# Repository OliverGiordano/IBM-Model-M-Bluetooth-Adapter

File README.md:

# IBM Model M Bluetooth Adapter

A Bluetooth adapter for the IBM Model M PS/2 keyboard. The adapter converts PS/2 signals from the keyboard to HID signals that are sent over Bluetooth to a computer.

<div align="center">

</div>

---

## Project Goals

When I started this project I wanted to create a wireless way for my IBM Model M keyboard to connect to my Apple computer. When I use the adapter I bought off Amazon, my MacBook thought my keyboard was a barcode reader, which was not ideal.

---

## Project Iterations

### Iteration 1 — Custom Controller Replacement

My first attempt was to replace the control board on my keyboard entirely with a custom solution. The main advantage of this method was power efficiency — the giant microcontroller in the Model M is very old and eats energy. When plugged into a desktop this doesn't cause a problem, but on a limited battery it could be an issue.

<div align="center">

</div>

After some initial testing I chose to scrap this idea for a few reasons:

- I needed to disassemble the keyboard every time I wanted to work on the adapter, then reassemble it every time I wanted to use it.
- The membrane requires 26 GPIO ports to interface with the matrix. This was doable with an I2C GPIO extender, but it made the breadboarded prototype very difficult to debug since each connection was a new point of failure.
- It required using terrible membrane connectors.

<div align="center">

</div>

---

### Iteration 2 — PS/2 Adapter

My second iteration was creating an adapter that plugs into the Model M's PS/2 output. This was very convenient because I could cut one head off an existing adapter and directly break out the wiring. This solution is easy to wire and test because the PS/2 standard only has 4 wires: Data, Clock, 5V, and GND.

<div align="center">

</div>

For this project I chose to use the **Adafruit Feather ESP32**. I chose this microcontroller because it has built-in Bluetooth and a built-in battery circuit, and it was only around $8 — great for my budget.

One problem I didn't realize when picking it was that the Model M and the PS/2 standard require 5V input, but the Feather only supplies 3.3V. Because of this, I currently pull power for the PS/2 directly from the 5V USB line, which means the adapter needs to be plugged into a power source for now since the battery cannot supply 5V. In the future I plan to add a voltage booster for the 3.3V line, but it hasn't arrived yet.

Since reading 5V on the Feather would destroy the microcontroller, I use **voltage dividers** on the Data and Clock lines. Each divider consists of 3 resistors of equal resistance, with two wired in series.

<div align="center">

</div>

---

## Updates

Fixing the issue of the Feather not being able to supply 5V for the keyboard, I updated my design to include a voltage booster. The voltage booster I choose to use was the MT3608, a voltage booster that could vary output with a variable resistor.  I connected it to a PSU and set the PSU to 3.3V, then used a multimeter to mesure the voltage as I adjusted the resistor.

When attaching the voltage booster I re-wired the rest of the board to be more durrable and fit into a smaller space, here was my final build front and back:

I also have been working on making a single PCB for the design to continue improving its durability and decreasing size unfortunatly it is a little out of my budget and I don't have the tools I will need to assemble it so that portion will be tabled for now.

here are my schematics and layouts:

---

## Software

The code uses 3 libraries:

- **PS2KeyAdvanced** — reads the serial output from the keyboard
- **PS2KeyMap** — maps PS2KeyAdvanced output to proper HID commands
- **BleKeyboard** — sends HID commands via Bluetooth

PS2KeyMap works for about 90% of keys. For the remaining 10%, I manually printed the output from PS2KeyAdvanced key by key and mapped them through a switch statement.

The code also reports battery level. The Adafruit Feather maps the battery voltage through an internal divider to analog pin 13 (GPIO 35), so to read the voltage I read GPIO 35 and multiply by two.

---

## Known Issues

The lock keys (Caps Lock, Scroll Lock, Num Lock) do not light up their respective LEDs. At first, pressing these keys froze the keyboard entirely. To fix this, I went into the PS2KeyAdvanced library and remapped the lock keys to keys not present on my keyboard, then handled them manually in code.

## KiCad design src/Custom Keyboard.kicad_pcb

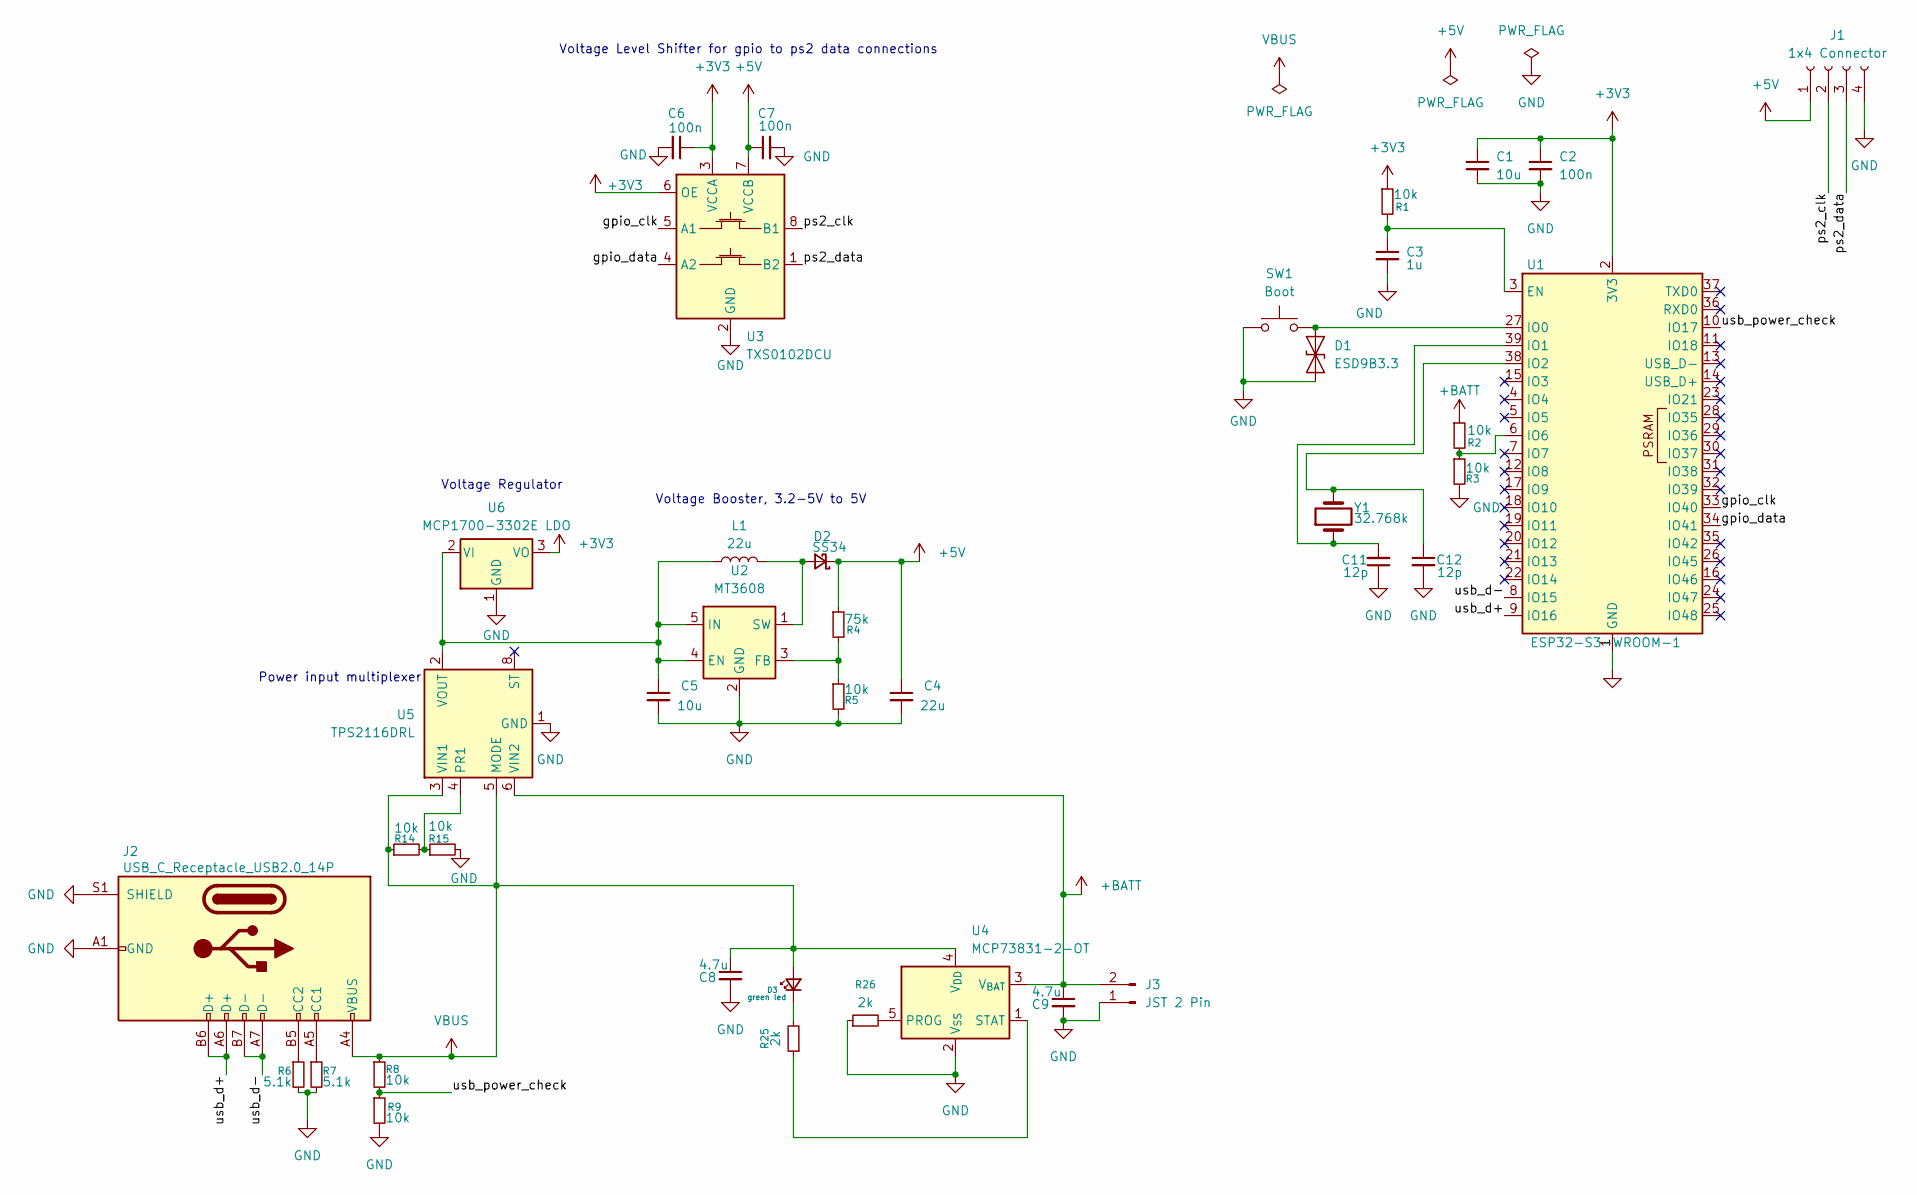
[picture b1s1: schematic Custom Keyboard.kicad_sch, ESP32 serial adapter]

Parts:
C1, C5: 10u; C_0402_1005Metric_Pad0.74x0.62mm_HandSolder
C2, C6, C7: 100n; C_0402_1005Metric_Pad0.74x0.62mm_HandSolder
C3: 1u; C_0402_1005Metric_Pad0.74x0.62mm_HandSolder
C4: 22u; C_0402_1005Metric_Pad0.74x0.62mm_HandSolder
C8, C9: 4.7u; C_0402_1005Metric_Pad0.74x0.62mm_HandSolder
C11, C12: 12p; C_0402_1005Metric_Pad0.74x0.62mm_HandSolder
D1: ESD9B3.3; D_SOD-923
D2: SS34; D_SOD-123F
D3: green led; LED_0402_1005Metric
J1: 1x4 Connector; PinHeader_1x04_P1.27mm_Vertical
J2: USB_C_Receptacle_USB2.0_14P; USB_C_Receptacle_HRO_TYPE-C-31-M-12
J3: JST 2 Pin; JST_ACH_BM02B-ACHSS-GAN-ETF_1x02-1MP_P1.20mm_Vertical
L1: 22u; L_Bourns_SRR1260
R1, R2, R3, R5, R8, R9, R14, R15: 10k; R_0402_1005Metric_Pad0.72x0.64mm_HandSolder
R4: 75k; R_0402_1005Metric_Pad0.72x0.64mm_HandSolder
R6, R7: 5.1k; R_0402_1005Metric_Pad0.72x0.64mm_HandSolder
R25, R26: 2k; R_0402_1005Metric_Pad0.72x0.64mm_HandSolder
SW1: Boot; SW_SPST_Omron_B3FS-100xP
U1: ESP32-S3-WROOM-1
U2: MT3608; SOT-23-6
U3: TXS0102DCU; VSSOP-8_2.3x2mm_P0.5mm
U4: MCP73831-2-OT; SOT-23-5
U5: TPS2116DRL; SOT-583-8
U6: MCP1700-3302E LDO; SOT-89-3
Y1: 32.768k; Crystal_SMD_3215-2Pin_3.2x1.5mm

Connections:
+3V3: C1.1, C2.1, C6.1, R1.1, U1.2 (3V3), U3.3 (VCCA), U3.6 (OE), U6.3 (VO)
+5V: C4.1, C7.1, D2.1 (K), J1.1, R4.1, U3.7 (VCCB)
+BATT: C9.1, J3.2, R2.1, U4.3 (V_{BAT}), U5.6 (VIN2)
/gpio_clk: U1.33 (IO40), U3.5 (A1)
/gpio_data: U1.34 (IO41), U3.4 (A2)
/ps2_clk: J1.2, U3.8 (B1)
/ps2_data: J1.3, U3.1 (B2)
/usb_d+: J2.A6 (D+), J2.B6 (D+), U1.9 (IO16)
/usb_d-: J2.A7 (D-), J2.B7 (D-), U1.8 (IO15)
/usb_power_check: R8.2, R9.1, U1.10 (IO17)
GND: C1.2, C2.2, C3.2, C4.2, C5.2, C6.2, C7.2, C8.2, C9.2, C11.1, C12.2, D1.1 (A1), J1.4, J2.A1 (GND), J2.A12 (GND), J2.B1 (GND), J2.B12 (GND), J2.S1 (SHIELD), J3.1, R3.2, R5.2, R6.2, R7.2, R9.2, R15.2, R26.1, SW1.1, U1.1 (GND), U1.40 (GND), U1.41 (GND), U2.2 (GND), U3.2 (GND), U4.2 (V_{SS}), U5.1 (GND), U6.1 (GND)
unnamed: D1.2 (A2), SW1.2, U1.27 (IO0)
unnamed: D2.2 (A), L1.2, U2.1 (SW)
unnamed: D3.1 (K), R25.2
unnamed: J2.A5 (CC1), R7.1
unnamed: J2.B5 (CC2), R6.1
unnamed: C3.1, R1.2, U1.3 (EN)
unnamed: C11.2, U1.39 (IO1), Y1.1
unnamed: C12.1, U1.38 (IO2), Y1.2
unnamed: R2.2, R3.1, U1.6 (IO6)
unnamed: C5.1, L1.1, U2.4 (EN), U2.5 (IN), U5.2 (VOUT), U5.7 (VOUT), U6.2 (VI)
unnamed: R4.2, R5.1, U2.3 (FB)
unnamed: R26.2, U4.5 (PROG)
unnamed: R25.1, U4.1 (STAT)
unnamed: R14.2, R15.1, U5.4 (PR1)
VBUS: C8.1, D3.2 (A), J2.A4 (VBUS), J2.A9 (VBUS), J2.B4 (VBUS), J2.B9 (VBUS), R8.1, R14.1, U4.4 (V_{DD}), U5.3 (VIN1), U5.5 (MODE)

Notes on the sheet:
Voltage Booster, 3.2-5V to 5V
Power input multiplexer
Voltage Level Shifter for gpio to ps2 data connections
Voltage Regulator

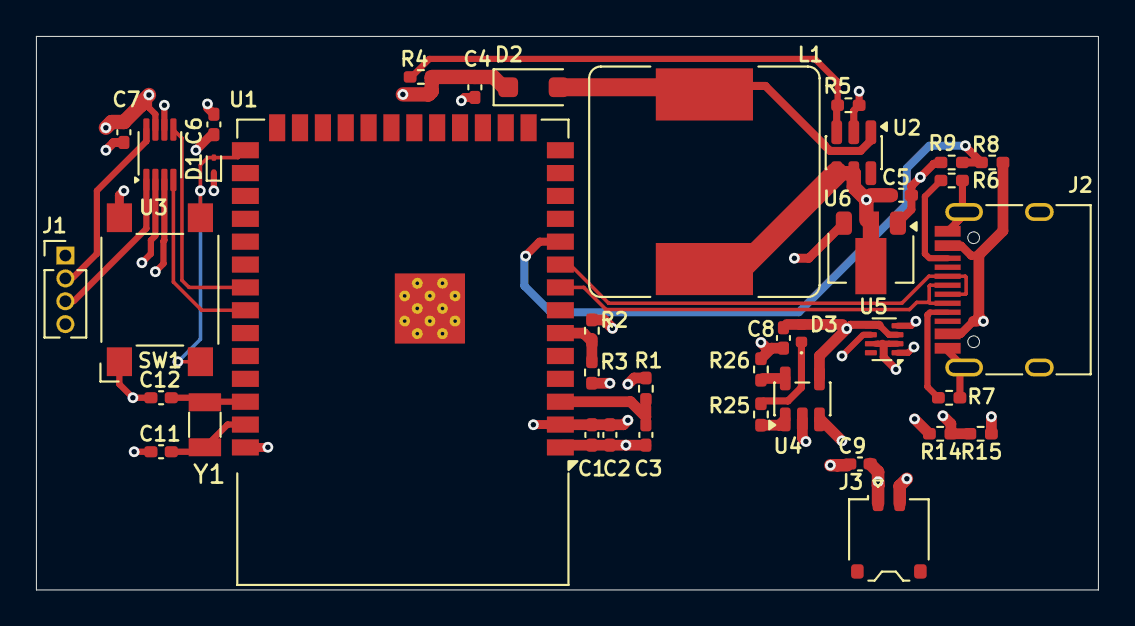
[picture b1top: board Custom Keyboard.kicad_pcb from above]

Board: 4 copper layers, 59.0 x 30.8 mm, 39 parts (0 on the bottom side), 26 nets.

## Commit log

2026-03-28 Enhance README formatting and image styles
    Updated formatting for project goals and iterations sections in README.md. Added styles to images for better presentation.
2026-03-28 Revise README for clarity and completeness
    Updated README to enhance project goals, iterations, software details, and known issues.
2026-03-28 Update README with images and formatting enhancements
    Added images and improved formatting for project iterations.
2026-05-13 Document updates on design improvements and voltage booster
    Added section detailing updates to the design, including the integration of a voltage booster and improvements in wiring for durability and size.
2026-05-13 Add custom pcb files
